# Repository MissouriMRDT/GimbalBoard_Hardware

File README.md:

# GimbalBoard_Hardware
Controls position of multiple servos using PWM.

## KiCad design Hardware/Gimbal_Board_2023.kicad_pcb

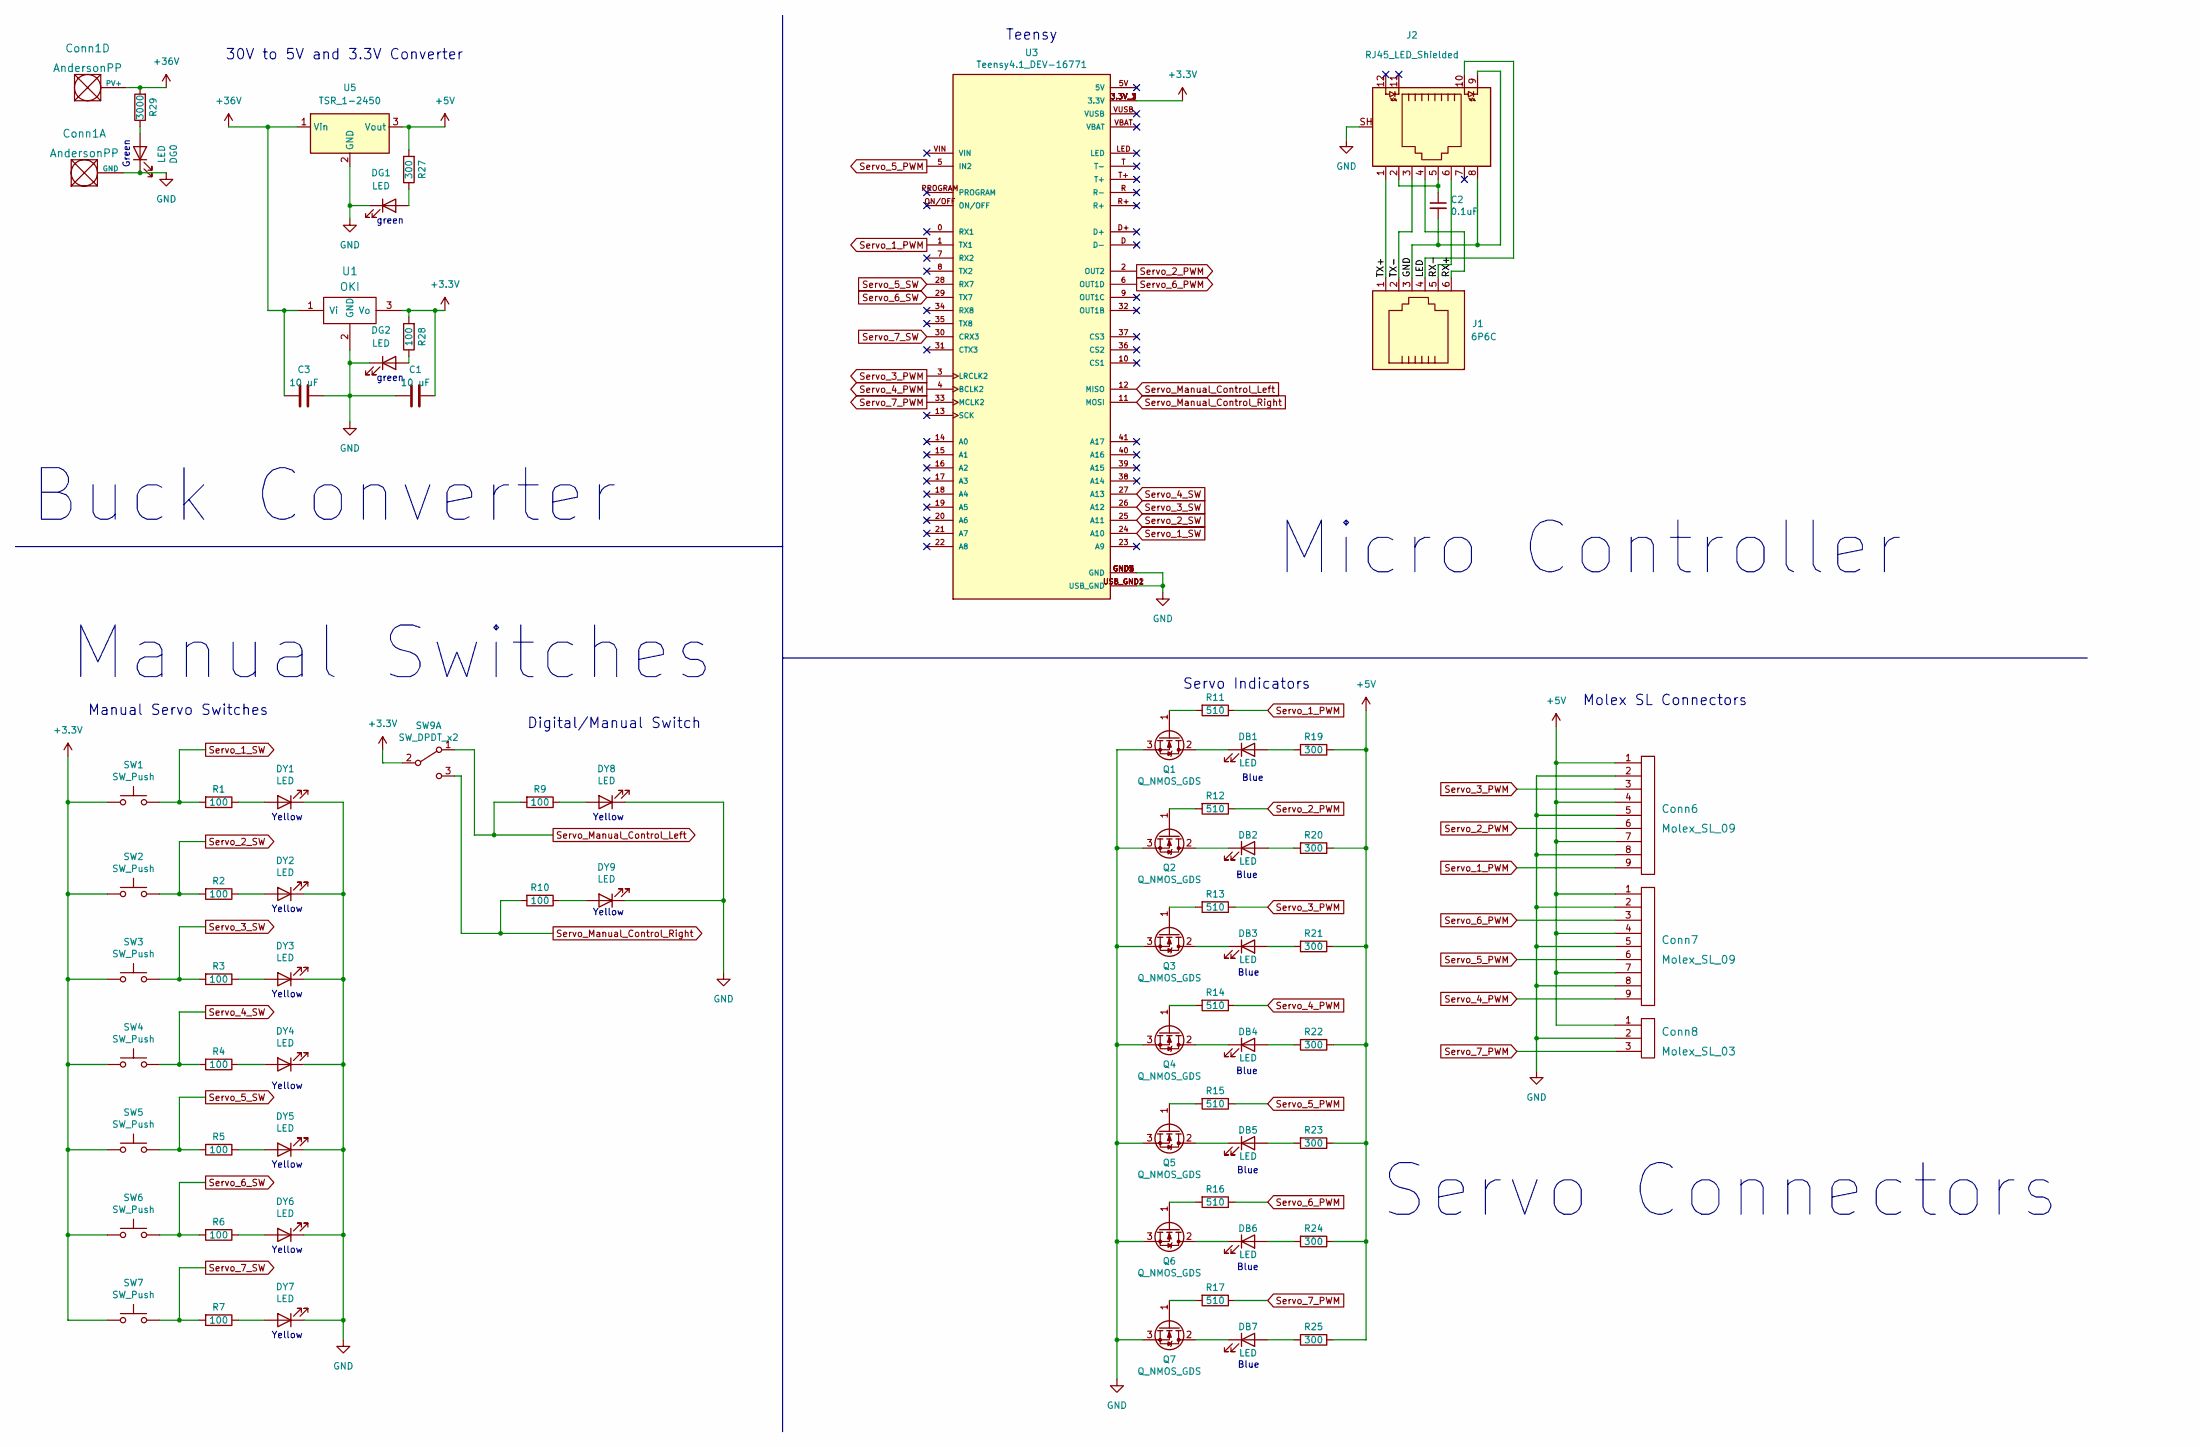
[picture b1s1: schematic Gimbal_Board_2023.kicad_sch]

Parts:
C1, C3: 10 uF; C_0603_1608Metric_Pad1.08x0.95mm_HandSolder
C2: 0.1uF; C_0603_1608Metric_Pad1.08x0.95mm_HandSolder
Conn1: AndersonPP; Square_Anderson_2_H_Side_By_Side_PV
Conn6, Conn7: Molex_SL_09; MOLEX_SL_09_Horizontal
Conn8: Molex_SL_03; MOLEX_SL_03_Horizontal
DB1, DB2, DB3, DB4, DB5, DB6, DB7: LED; LED_0603_1608Metric_Pad1.05x0.95mm_HandSolder
DG0, DG1, DG2: LED; LED_0603_1608Metric_Pad1.05x0.95mm_HandSolder
DY1, DY2, DY3, DY4, DY5, DY6, DY7, DY8, DY9: LED; LED_0603_1608Metric_Pad1.05x0.95mm_HandSolder
J1: 6P6C; PinHeader_2x03_P2.00mm_Vertical
J2: RJ45_LED_Shielded; RJ45_Teensy
Q1, Q2, Q3, Q4, Q5, Q6, Q7: Q_NMOS_GDS; SOT-23
R1, R2, R3, R4, R5, R6, R7, R9, R10, R28: 100; R_0603_1608Metric_Pad0.98x0.95mm_HandSolder
R11, R12, R13, R14, R15, R16, R17: 510; R_0603_1608Metric_Pad0.98x0.95mm_HandSolder
R19, R20, R21, R22, R23, R24, R25, R27: 300; R_0603_1608Metric_Pad0.98x0.95mm_HandSolder
R29: 3000; R_0603_1608Metric_Pad0.98x0.95mm_HandSolder
SW1, SW2, SW3, SW4, SW5, SW6, SW7: SW_Push; SW_SPST_EVPBF
SW9: SW_DPDT_x2; SW_Slide_1P2T_CK_OS102011MS2Q
U1: OKI; OKI_Horizontal
U3: Teensy4.1_DEV-16771; MODULE_DEV-16771; PARTREV 4.1
U5: TSR_1-2450; Converter_DCDC_TRACO_TSR-1_THT

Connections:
+3.3V: C1.2, R28.2, SW1.2, SW2.1, SW3.1, SW4.1, SW5.1, SW6.1, SW7.1, SW9.2 (B), U1.3 (Vo), U3.3.3V_1 (3.3V), U3.3.3V_2 (3.3V), U3.3.3V_3 (3.3V)
+5V: Conn6.1, Conn6.4, Conn6.7, Conn7.1, Conn7.4, Conn7.7, Conn8.1, R19.1, R20.1, R21.1, R22.1, R23.1, R24.1, R25.1, R27.2, U5.3 (Vout)
+36V: C3.1, Conn1.4 (PV+), R29.2, U1.1 (Vi), U5.1 (Vin)
/LED: J1.4, J2.10
/RX+: J1.6, J2.4
/RX-: J1.5, J2.6
/TX+: J1.1, J2.1
/TX-: J1.2, J2.3
GND: C1.1, C2.2, C3.2, Conn1.1 (GND), Conn6.2, Conn6.5, Conn6.8, Conn7.2, Conn7.5, Conn7.8, Conn8.2, DG0.1 (K), DG1.1 (K), DG2.1 (K), DY1.1 (K), DY2.1 (K), DY3.1 (K), DY4.1 (K), DY5.1 (K), DY6.1 (K), DY7.1 (K), DY8.1 (K), DY9.1 (K), J1.3, J2.8, J2.9, J2.SH, Q1.3 (S), Q2.3 (S), Q3.3 (S), Q4.3 (S), Q5.3 (S), Q6.3 (S), Q7.3 (S), U1.2 (GND), U3.GND1 (GND), U3.GND2 (GND), U3.GND3 (GND), U3.GND4 (GND), U3.GND5 (GND), U3.USB_GND1 (USB_GND), U3.USB_GND2 (USB_GND), U5.2 (GND)
unnamed: C2.1, J2.2, J2.5
unnamed: DB1.1 (K), Q1.2 (D)
unnamed: DB1.2 (A), R19.2
unnamed: DB2.1 (K), Q2.2 (D)
unnamed: DB2.2 (A), R20.2
unnamed: DB3.1 (K), Q3.2 (D)
unnamed: DB3.2 (A), R21.2
unnamed: DB4.1 (K), Q4.2 (D)
unnamed: DB4.2 (A), R22.2
unnamed: DB5.1 (K), Q5.2 (D)
unnamed: DB5.2 (A), R23.2
unnamed: DB6.1 (K), Q6.2 (D)
unnamed: DB6.2 (A), R24.2
unnamed: DB7.1 (K), Q7.2 (D)
unnamed: DB7.2 (A), R25.2
unnamed: DG0.2 (A), R29.1
unnamed: DG1.2 (A), R27.1
unnamed: DG2.2 (A), R28.1
unnamed: DY1.2 (A), R1.1
unnamed: DY2.2 (A), R2.1
unnamed: DY3.2 (A), R3.1
unnamed: DY4.2 (A), R4.1
unnamed: DY5.2 (A), R5.1
unnamed: DY6.2 (A), R6.1
unnamed: DY7.2 (A), R7.1
unnamed: DY8.2 (A), R9.1
unnamed: DY9.2 (A), R10.1
unnamed: Q1.1 (G), R11.2
unnamed: Q2.1 (G), R12.2
unnamed: Q3.1 (G), R13.2
unnamed: Q4.1 (G), R14.2
unnamed: Q5.1 (G), R15.2
unnamed: Q6.1 (G), R16.2
unnamed: Q7.1 (G), R17.2
Servo_1_PWM: Conn6.9, R11.1, U3.1 (TX1)
Servo_1_SW: R1.2, SW1.1, U3.24 (A10)
Servo_2_PWM: Conn6.6, R12.1, U3.2 (OUT2)
Servo_2_SW: R2.2, SW2.2, U3.25 (A11)
Servo_3_PWM: Conn6.3, R13.1, U3.3 (LRCLK2)
Servo_3_SW: R3.2, SW3.2, U3.26 (A12)
Servo_4_PWM: Conn7.9, R14.1, U3.4 (BCLK2)
Servo_4_SW: R4.2, SW4.2, U3.27 (A13)
Servo_5_PWM: Conn7.6, R15.1, U3.5 (IN2)
Servo_5_SW: R5.2, SW5.2, U3.28 (RX7)
Servo_6_PWM: Conn7.3, R16.1, U3.6 (OUT1D)
Servo_6_SW: R6.2, SW6.2, U3.29 (TX7)
Servo_7_PWM: Conn8.3, R17.1, U3.33 (MCLK2)
Servo_7_SW: R7.2, SW7.2, U3.30 (CRX3)
Servo_Manual_Control_Left: R9.2, SW9.1 (A), U3.12 (MISO)
Servo_Manual_Control_Right: R10.2, SW9.3 (C), U3.11 (MOSI)

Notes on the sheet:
Yellow
Blue
Servo Indicators
Teensy
Manual Servo Switches
Molex SL Connectors
Buck Converter
green
Micro Controller
30V to 5V and 3.3V Converter
Manual Switches
Digital/Manual Switch
Green
Servo Connectors

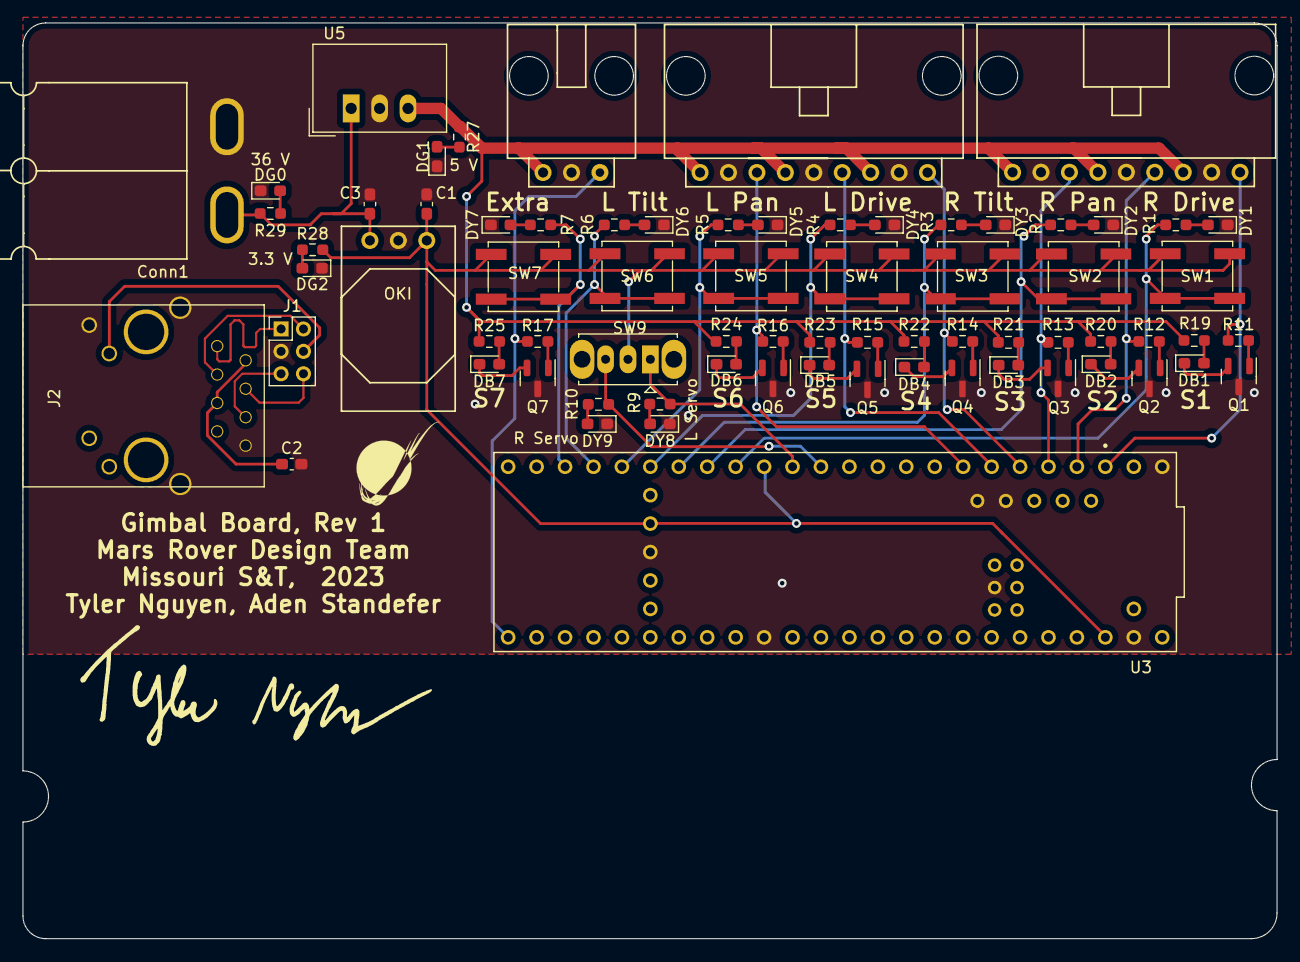
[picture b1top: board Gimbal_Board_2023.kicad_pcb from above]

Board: 2 copper layers, 112.0 x 81.8 mm, 72 parts (0 on the bottom side), 59 nets.

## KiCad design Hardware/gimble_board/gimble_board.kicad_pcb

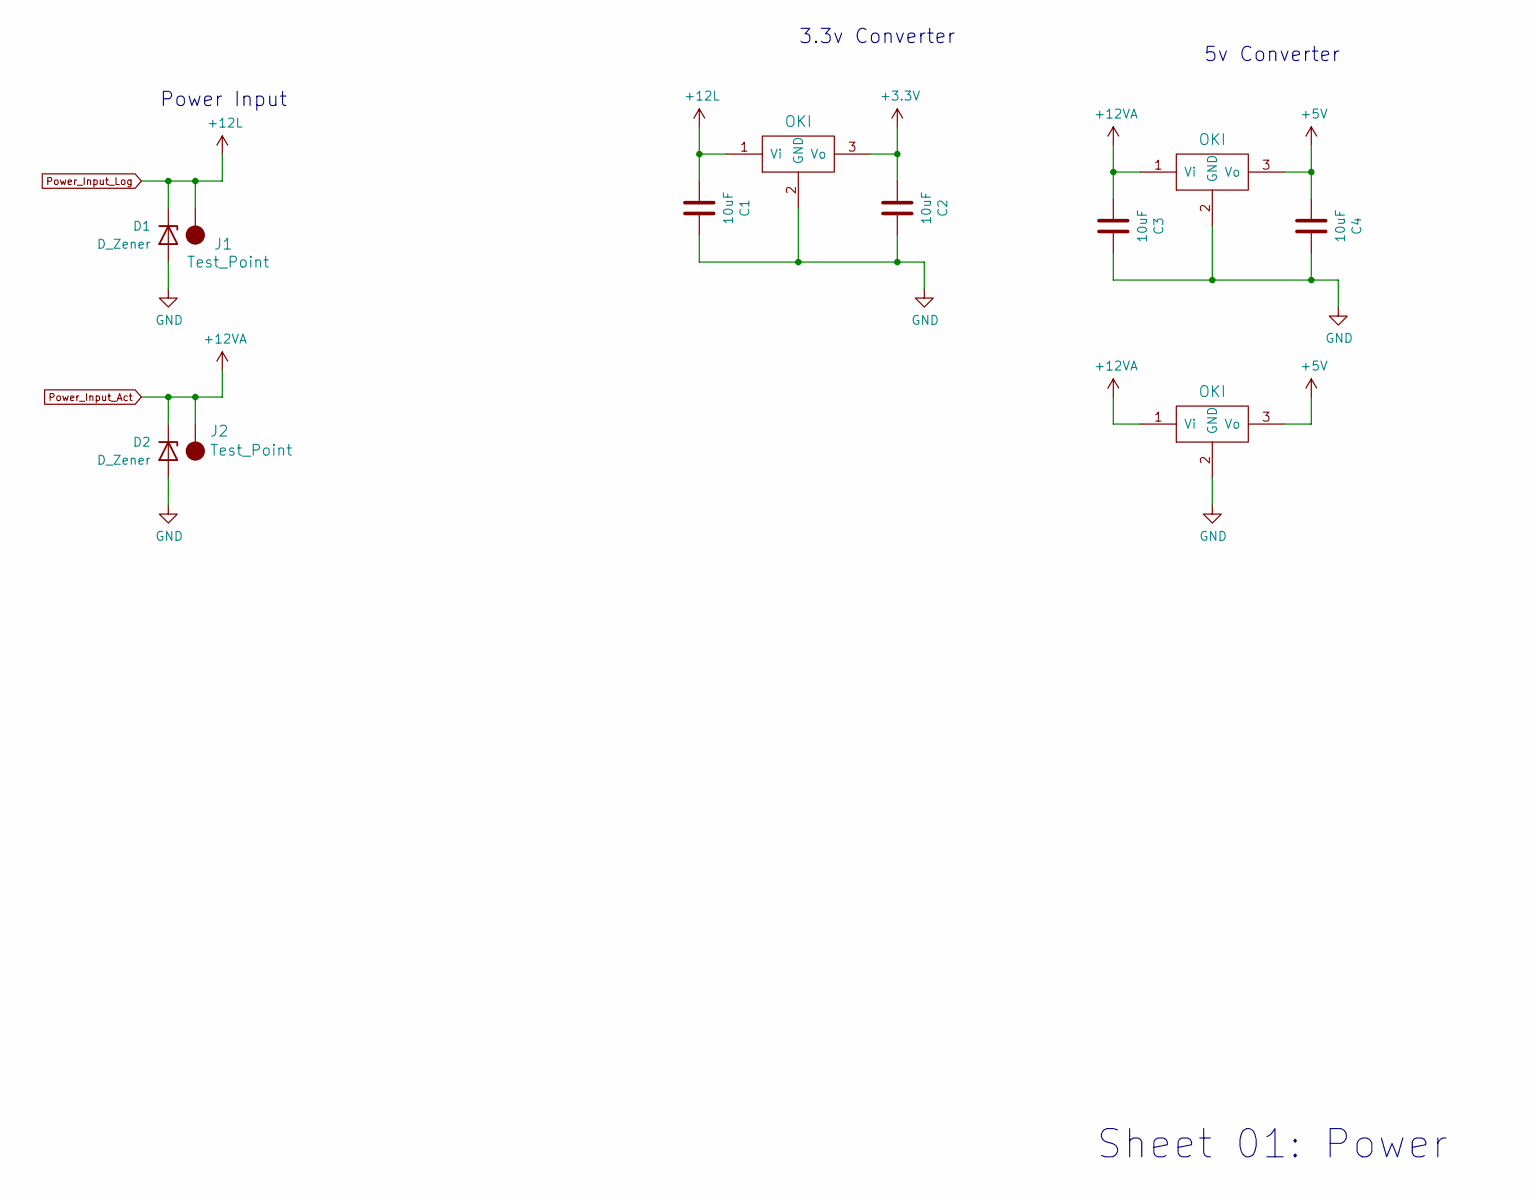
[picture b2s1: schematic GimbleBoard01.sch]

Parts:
C1, C2, C3, C4: 10uF; C_0603_1608Metric_Pad1.05x0.95mm_HandSolder
D1, D2: D_Zener; D_0201_0603Metric_Pad0.64x0.40mm_HandSolder
J1, J2: Test_Point; TestPoint_Pad_2.0x2.0mm
U1, U2, U4: OKI; OKI_Horizontal

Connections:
+3V3: C2.2, U1.3 (Vo); also elsewhere on the board
+5V: C4.2, U2.3 (Vo), U4.3 (Vo); also elsewhere on the board
GND: C1.1, C2.1, C3.1, C4.1, D1.2 (A), D2.2 (A), U1.2 (GND), U2.2 (GND), U4.2 (GND); also elsewhere on the board
Power_Input_Act: C3.2, D2.1 (K), J2.1, U2.1 (Vi), U4.1 (Vi); also elsewhere on the board
Power_Input_Log: C1.2, D1.1 (K), J1.1, U1.1 (Vi); also elsewhere on the board

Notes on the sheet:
Sheet 01: Power
Power Input
3.3v Converter
5v Converter

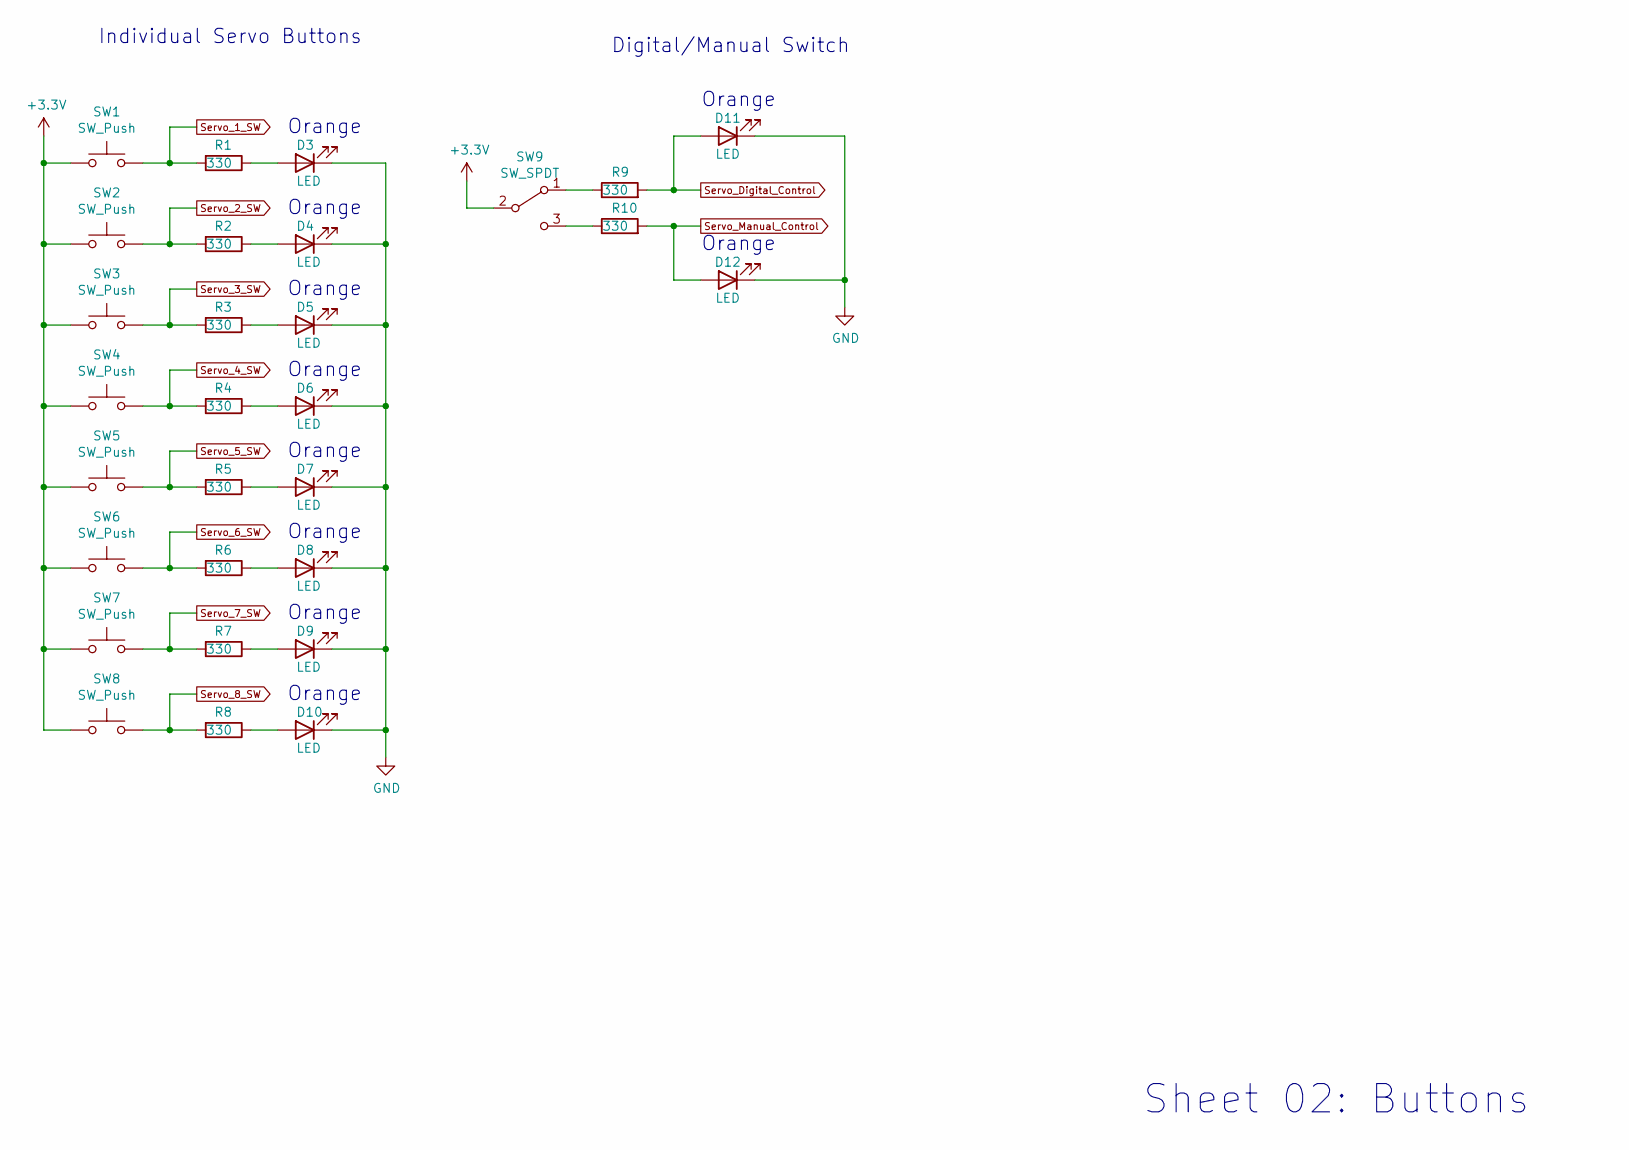
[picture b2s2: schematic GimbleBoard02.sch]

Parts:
D3, D4, D5, D6, D7, D8, D9, D10, D11, D12: LED; LED_0603_1608Metric_Pad1.05x0.95mm_HandSolder
R1, R2, R3, R4, R5, R6, R7, R8, R9, R10: 330; R_0603_1608Metric_Pad1.05x0.95mm_HandSolder
SW1, SW2, SW3, SW4, SW5, SW6, SW7, SW8: SW_Push; SW_SPST_TL3305A
SW9: SW_SPDT; SW_CuK_OS102011MA1QN1_SPDT_Angled

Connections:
+3V3: SW1.1, SW2.1, SW3.1, SW4.1, SW5.1, SW6.1, SW7.1, SW8.1, SW9.2 (B); also elsewhere on the board
GND: D3.1 (K), D4.1 (K), D5.1 (K), D6.1 (K), D7.1 (K), D8.1 (K), D9.1 (K), D10.1 (K), D11.1 (K), D12.1 (K); also elsewhere on the board
unnamed: D3.2 (A), R1.1
unnamed: D4.2 (A), R2.1
unnamed: D5.2 (A), R3.1
unnamed: D6.2 (A), R4.1
unnamed: D7.2 (A), R5.1
unnamed: D8.2 (A), R6.1
unnamed: D9.2 (A), R7.1
unnamed: D10.2 (A), R8.1
unnamed: R9.1, SW9.1 (A)
unnamed: R10.1, SW9.3 (C)
Servo_1_SW: R1.2, SW1.2; also elsewhere on the board
Servo_2_SW: R2.2, SW2.2; also elsewhere on the board
Servo_3_SW: R3.2, SW3.2; also elsewhere on the board
Servo_4_SW: R4.2, SW4.2; also elsewhere on the board
Servo_5_SW: R5.2, SW5.2; also elsewhere on the board
Servo_6_SW: R6.2, SW6.2; also elsewhere on the board
Servo_7_SW: R7.2, SW7.2; also elsewhere on the board
Servo_8_SW: R8.2, SW8.2; also elsewhere on the board
Servo_Digital_Control: D11.2 (A), R9.2; also elsewhere on the board
Servo_Manual_Control: D12.2 (A), R10.2; also elsewhere on the board

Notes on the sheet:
Sheet 02: Buttons
Orange
Individual Servo Buttons
Digital/Manual Switch

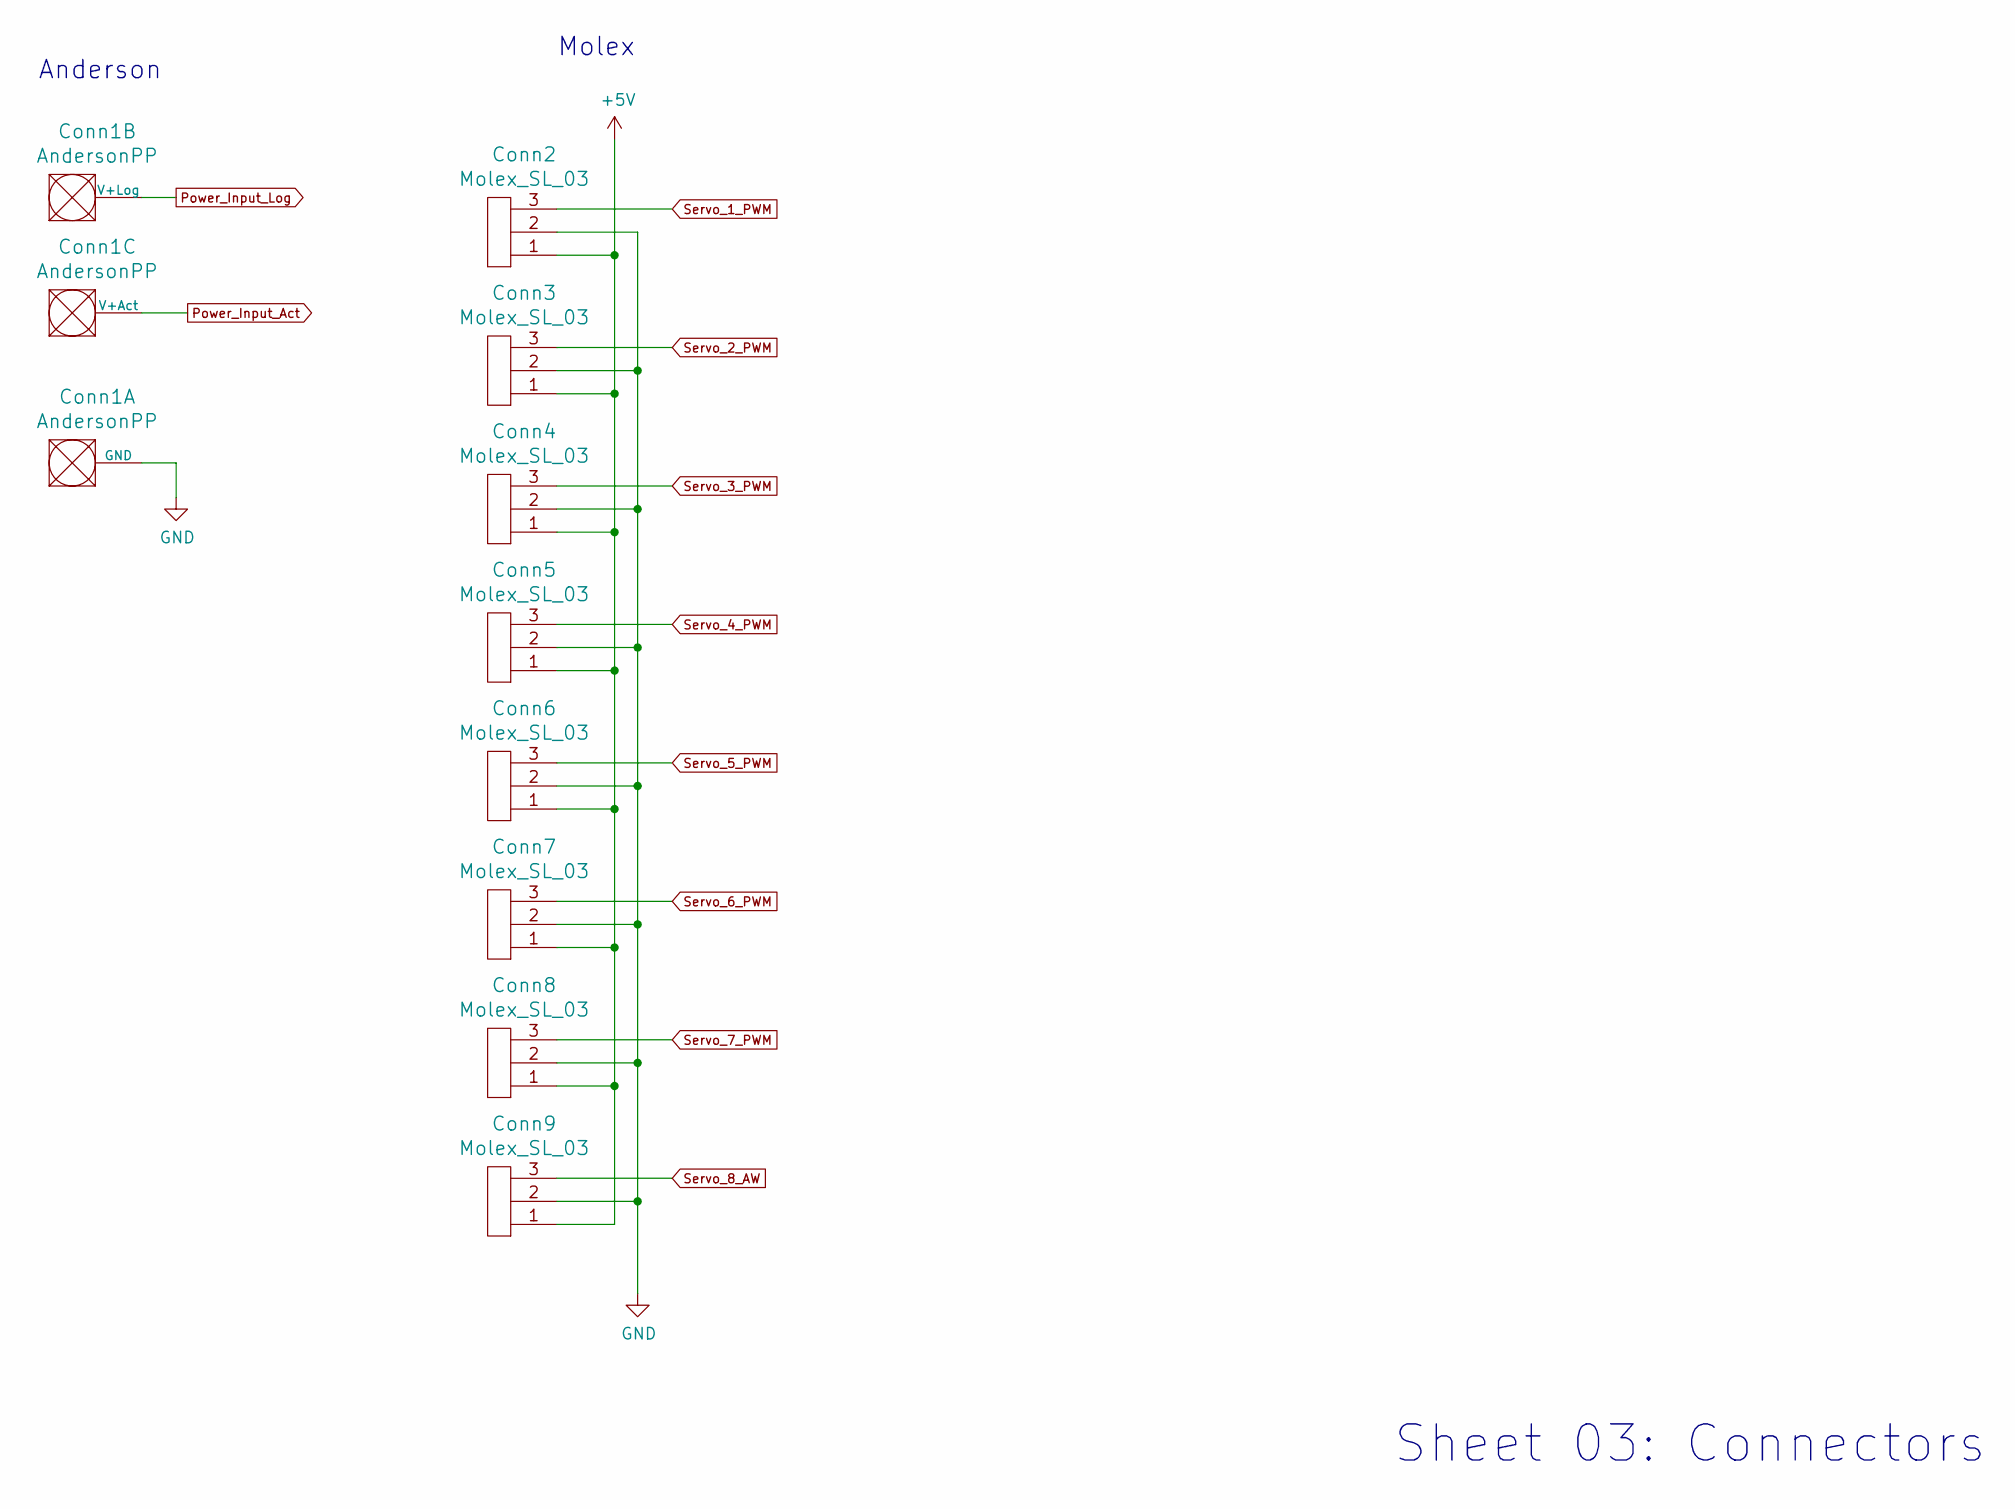
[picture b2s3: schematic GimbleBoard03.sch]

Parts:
Conn1: AndersonPP; Anderson_3_Horizontal_Side_by_Side
Conn2, Conn3, Conn4, Conn5, Conn6, Conn7, Conn8, Conn9: Molex_SL_03; MOLEX_SL_03_Horizontal

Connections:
+5V: Conn2.1, Conn3.1, Conn4.1, Conn5.1, Conn6.1, Conn7.1, Conn8.1, Conn9.1; also elsewhere on the board
GND: Conn1.1 (GND), Conn2.2, Conn3.2, Conn4.2, Conn5.2, Conn6.2, Conn7.2, Conn8.2, Conn9.2; also elsewhere on the board
Power_Input_Act: Conn1.3 (V+Act); also elsewhere on the board
Power_Input_Log: Conn1.2 (V+Log); also elsewhere on the board
Servo_1_PWM: Conn2.3; also elsewhere on the board
Servo_2_PWM: Conn3.3; also elsewhere on the board
Servo_3_PWM: Conn4.3; also elsewhere on the board
Servo_4_PWM: Conn5.3; also elsewhere on the board
Servo_5_PWM: Conn6.3; also elsewhere on the board
Servo_6_PWM: Conn7.3; also elsewhere on the board
Servo_7_PWM: Conn8.3; also elsewhere on the board
Servo_8_AW: Conn9.3; also elsewhere on the board

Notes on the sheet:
Sheet 03: Connectors
Anderson
Molex

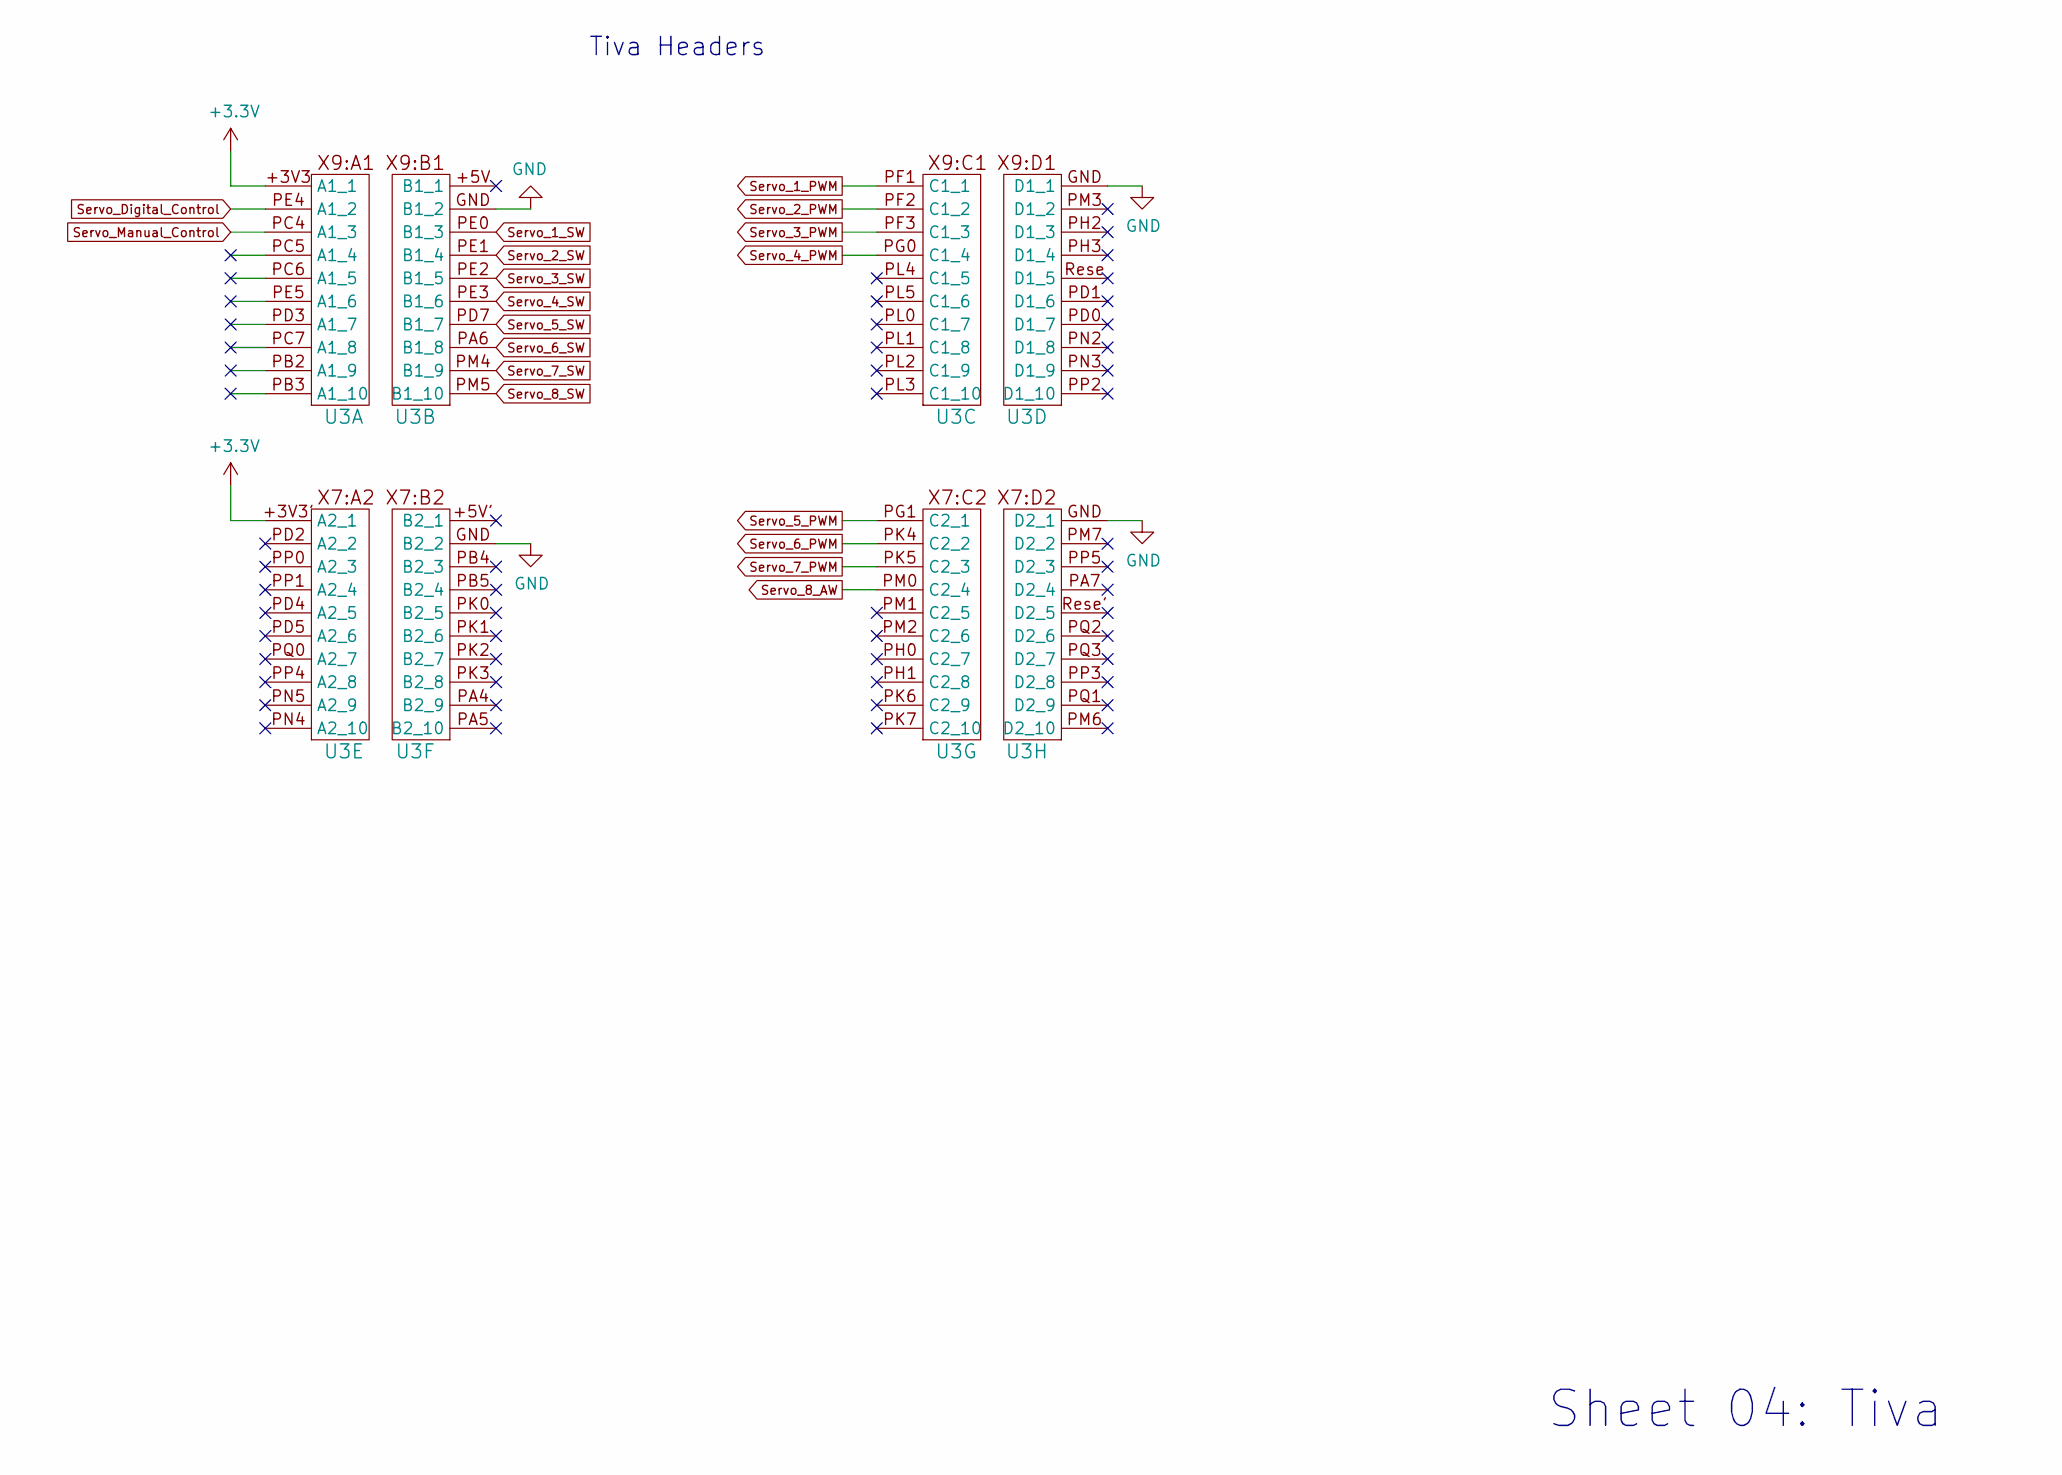
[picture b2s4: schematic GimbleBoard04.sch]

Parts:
U3: TM4C129E_Launchpad; TM4C129E_Launchpad_FULL_THT_BOTTOM

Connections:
+3V3: U3.+3V3 (A1_1), U3.+3V3' (A2_1); also elsewhere on the board
GND: U3.GND (B1_2); also elsewhere on the board
Servo_1_PWM: U3.PF1 (C1_1); also elsewhere on the board
Servo_1_SW: U3.PE0 (B1_3); also elsewhere on the board
Servo_2_PWM: U3.PF2 (C1_2); also elsewhere on the board
Servo_2_SW: U3.PE1 (B1_4); also elsewhere on the board
Servo_3_PWM: U3.PF3 (C1_3); also elsewhere on the board
Servo_3_SW: U3.PE2 (B1_5); also elsewhere on the board
Servo_4_PWM: U3.PG0 (C1_4); also elsewhere on the board
Servo_4_SW: U3.PE3 (B1_6); also elsewhere on the board
Servo_5_PWM: U3.PG1 (C2_1); also elsewhere on the board
Servo_5_SW: U3.PD7 (B1_7); also elsewhere on the board
Servo_6_PWM: U3.PK4 (C2_2); also elsewhere on the board
Servo_6_SW: U3.PA6 (B1_8); also elsewhere on the board
Servo_7_PWM: U3.PK5 (C2_3); also elsewhere on the board
Servo_7_SW: U3.PM4 (B1_9); also elsewhere on the board
Servo_8_AW: U3.PM0 (C2_4); also elsewhere on the board
Servo_8_SW: U3.PM5 (B1_10); also elsewhere on the board
Servo_Digital_Control: U3.PL0 (C1_7); also elsewhere on the board
Servo_Manual_Control: U3.PL1 (C1_8); also elsewhere on the board

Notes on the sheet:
Tiva Headers
Sheet 04: Tiva

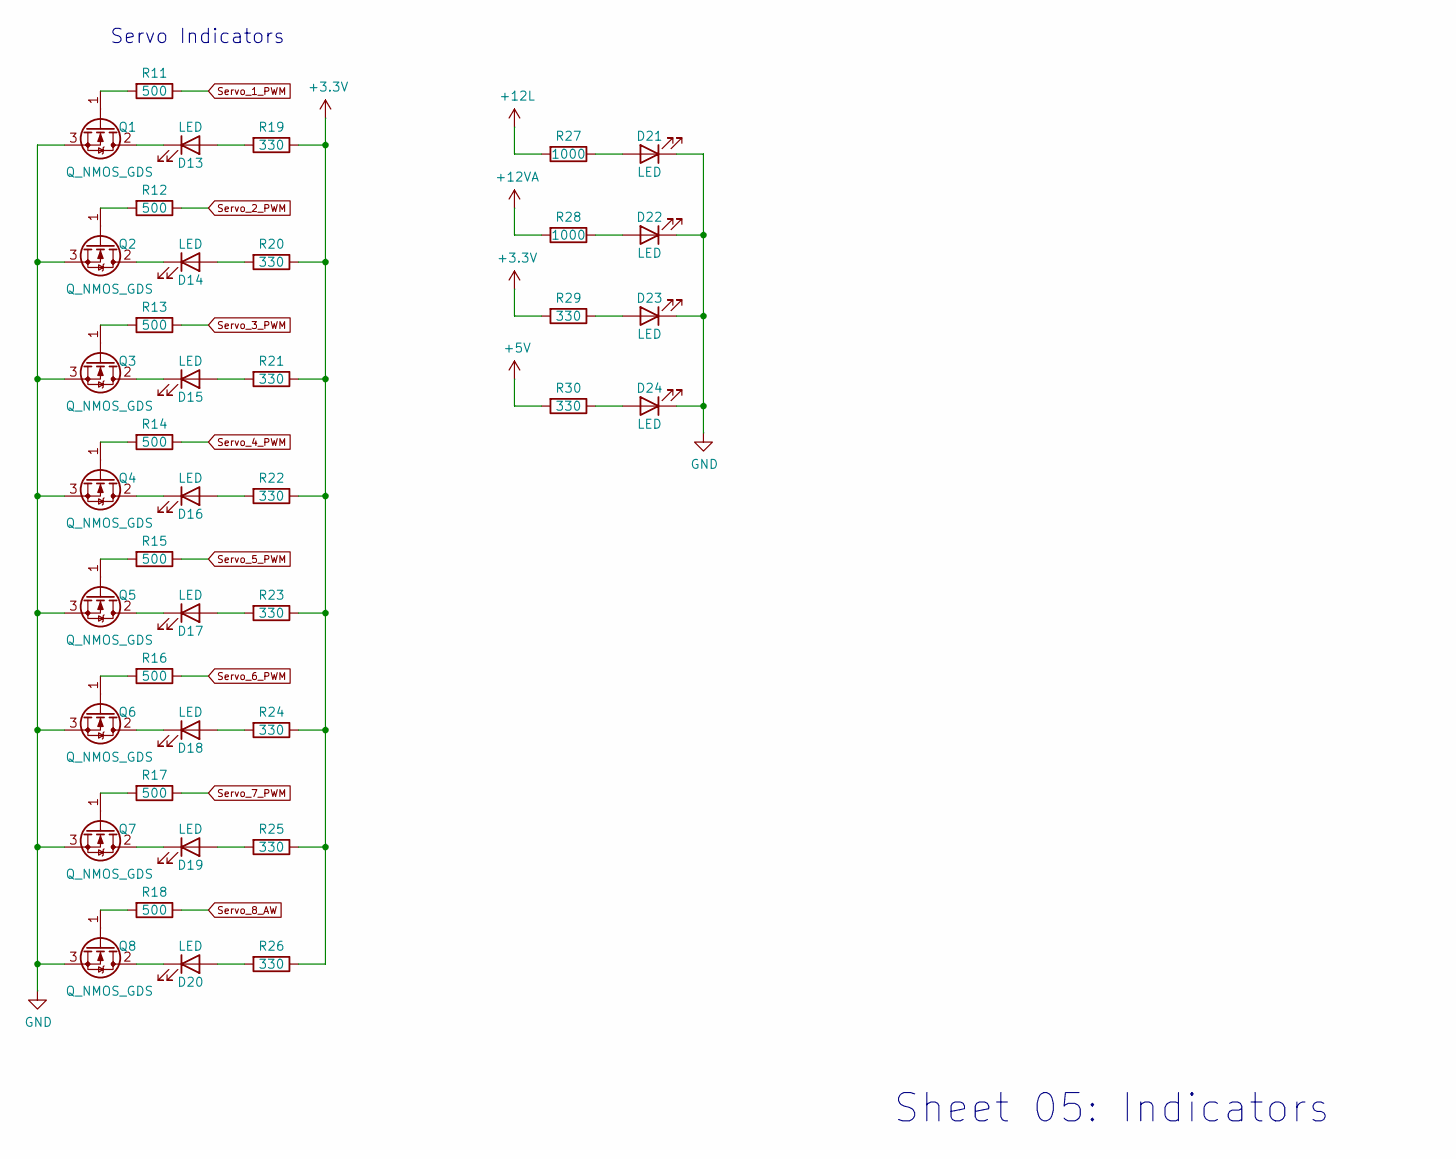
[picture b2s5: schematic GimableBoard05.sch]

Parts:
D13, D14, D15, D16, D17, D18, D19, D20, D21, D22, D23, D24: LED; LED_0603_1608Metric_Pad1.05x0.95mm_HandSolder
Q1, Q2, Q3, Q4, Q5, Q6, Q7, Q8: Q_NMOS_GDS; SOT-23_Handsoldering
R11, R12, R13, R14, R15, R16, R17, R18: 500; R_0603_1608Metric_Pad1.05x0.95mm_HandSolder
R19, R20, R21, R22, R23, R24, R25, R26, R29, R30: 330; R_0603_1608Metric_Pad1.05x0.95mm_HandSolder
R27, R28: 1000; R_0603_1608Metric_Pad1.05x0.95mm_HandSolder

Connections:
+3V3: R19.1, R20.1, R21.1, R22.1, R23.1, R24.1, R25.1, R26.1, R29.2; also elsewhere on the board
+5V: R30.2; also elsewhere on the board
GND: D21.1 (K), D22.1 (K), D23.1 (K), D24.1 (K), Q1.3 (S), Q2.3 (S), Q3.3 (S), Q4.3 (S), Q5.3 (S), Q6.3 (S), Q7.3 (S), Q8.3 (S); also elsewhere on the board
unnamed: D13.1 (K), Q1.2 (D)
unnamed: D13.2 (A), R19.2
unnamed: D14.1 (K), Q2.2 (D)
unnamed: D14.2 (A), R20.2
unnamed: D15.1 (K), Q3.2 (D)
unnamed: D15.2 (A), R21.2
unnamed: D16.1 (K), Q4.2 (D)
unnamed: D16.2 (A), R22.2
unnamed: D17.1 (K), Q5.2 (D)
unnamed: D17.2 (A), R23.2
unnamed: D18.1 (K), Q6.2 (D)
unnamed: D18.2 (A), R24.2
unnamed: D19.1 (K), Q7.2 (D)
unnamed: D19.2 (A), R25.2
unnamed: D20.1 (K), Q8.2 (D)
unnamed: D20.2 (A), R26.2
unnamed: D21.2 (A), R27.1
unnamed: D22.2 (A), R28.1
unnamed: D23.2 (A), R29.1
unnamed: D24.2 (A), R30.1
unnamed: Q1.1 (G), R11.2
unnamed: Q2.1 (G), R12.2
unnamed: Q3.1 (G), R13.2
unnamed: Q4.1 (G), R14.2
unnamed: Q5.1 (G), R15.2
unnamed: Q6.1 (G), R16.2
unnamed: Q7.1 (G), R17.2
unnamed: Q8.1 (G), R18.2
Power_Input_Act: R28.2; also elsewhere on the board
Power_Input_Log: R27.2; also elsewhere on the board
Servo_1_PWM: R11.1; also elsewhere on the board
Servo_2_PWM: R12.1; also elsewhere on the board
Servo_3_PWM: R13.1; also elsewhere on the board
Servo_4_PWM: R14.1; also elsewhere on the board
Servo_5_PWM: R15.1; also elsewhere on the board
Servo_6_PWM: R16.1; also elsewhere on the board
Servo_7_PWM: R17.1; also elsewhere on the board
Servo_8_AW: R18.1; also elsewhere on the board

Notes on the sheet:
Servo Indicators
Sheet 05: Indicators
